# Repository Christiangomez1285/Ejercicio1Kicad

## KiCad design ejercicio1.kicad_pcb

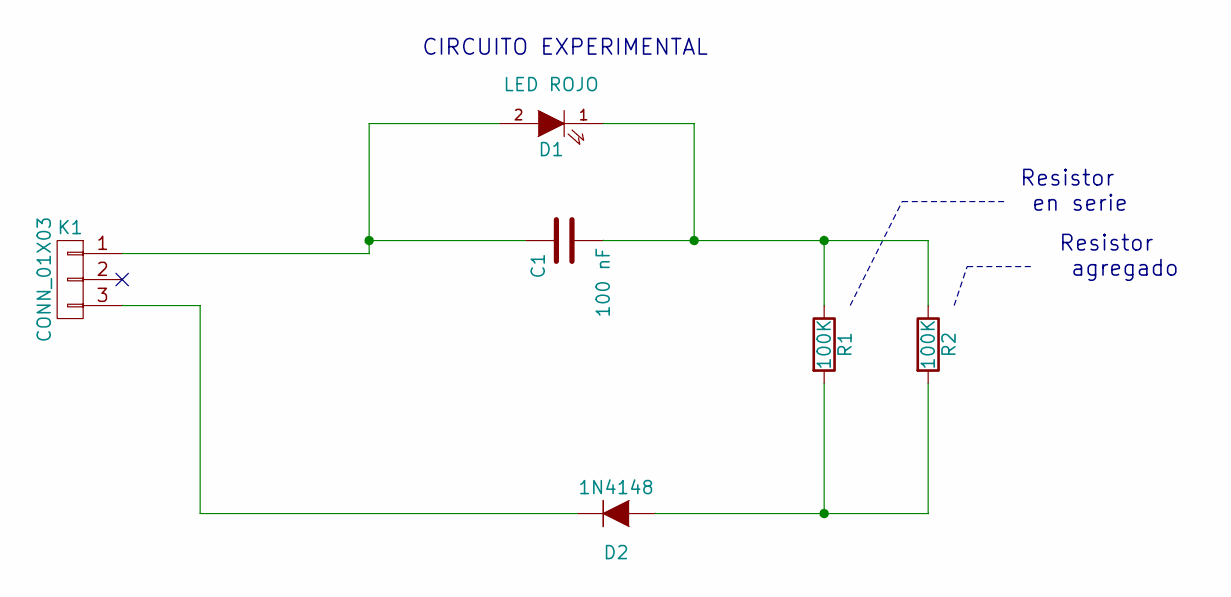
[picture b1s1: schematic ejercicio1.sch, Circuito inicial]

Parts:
C1: 100 nF; C_Rect_L7_W3.5_P5
D1: LED ROJO; LED-3MM
D2: 1N4148; Diode_DO-35_SOD27_Horizontal_RM10
K1: CONN_01X03; bornier3
R1, R2: 100K; R3-LARGE_PADS

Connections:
unnamed: C1.1, D1.1 (K), R1.1, R2.1
unnamed: C1.2, D1.2 (A), K1.1
unnamed: D2.1 (K), K1.3
unnamed: D2.2 (A), R1.2, R2.2

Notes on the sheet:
Resistor en serie
CIRCUITO EXPERIMENTAL
Resistor agregado

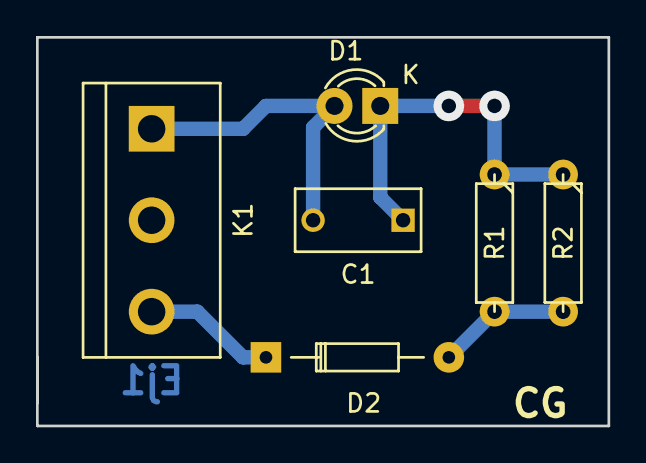
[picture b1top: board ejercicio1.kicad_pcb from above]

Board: 2 copper layers, 31.8 x 21.6 mm, 6 parts (0 on the bottom side), 4 nets.

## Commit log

2016-06-11 Commit message
